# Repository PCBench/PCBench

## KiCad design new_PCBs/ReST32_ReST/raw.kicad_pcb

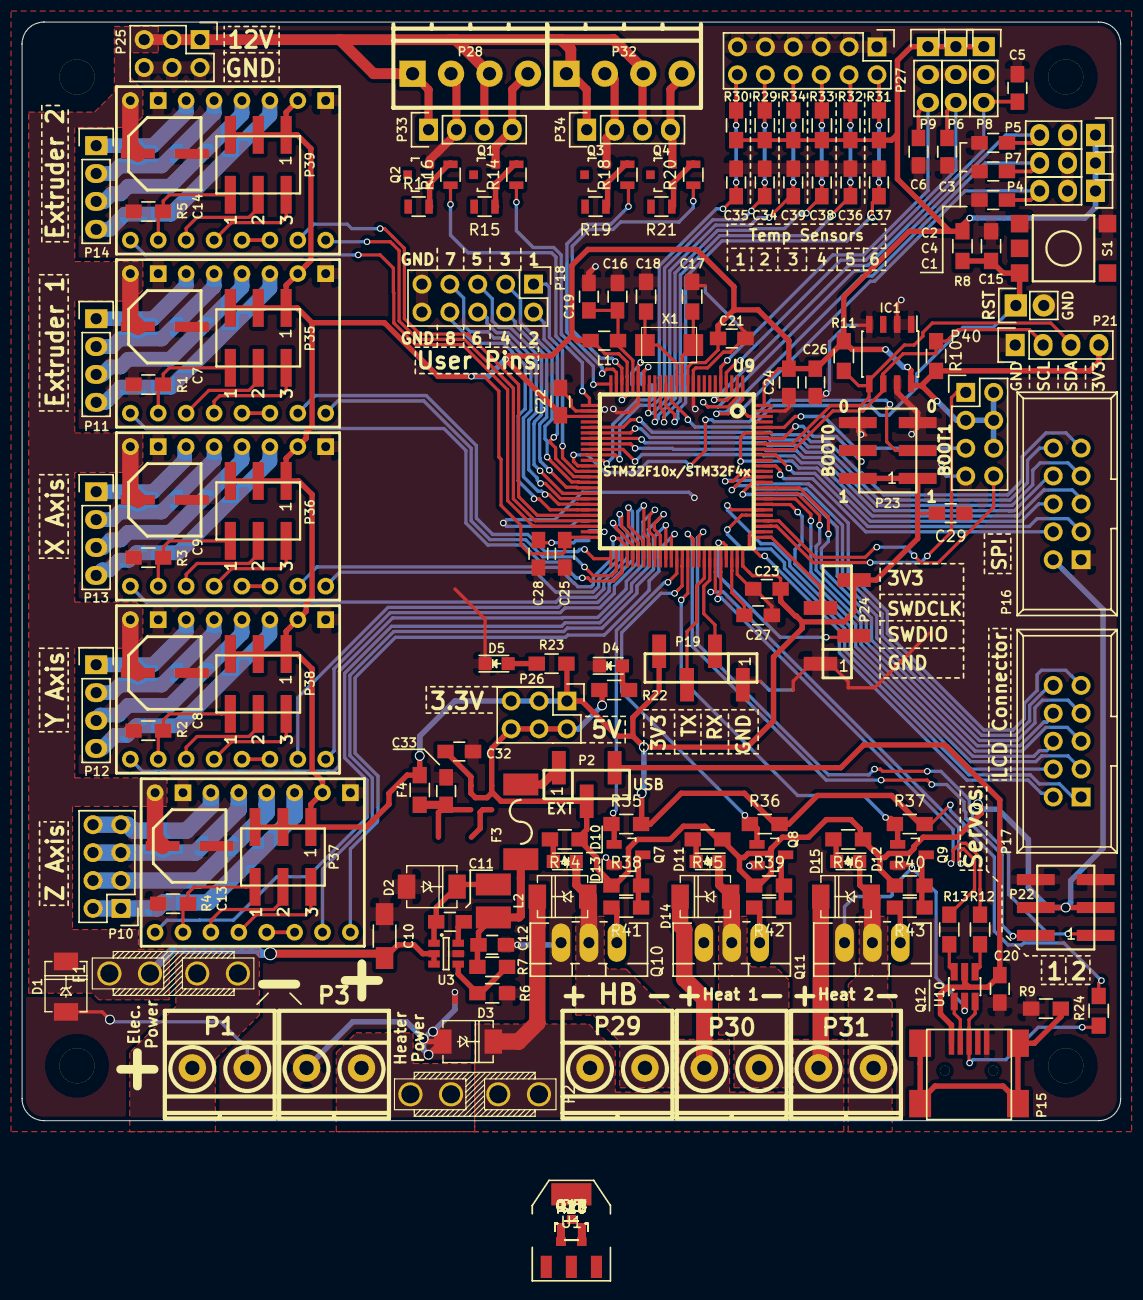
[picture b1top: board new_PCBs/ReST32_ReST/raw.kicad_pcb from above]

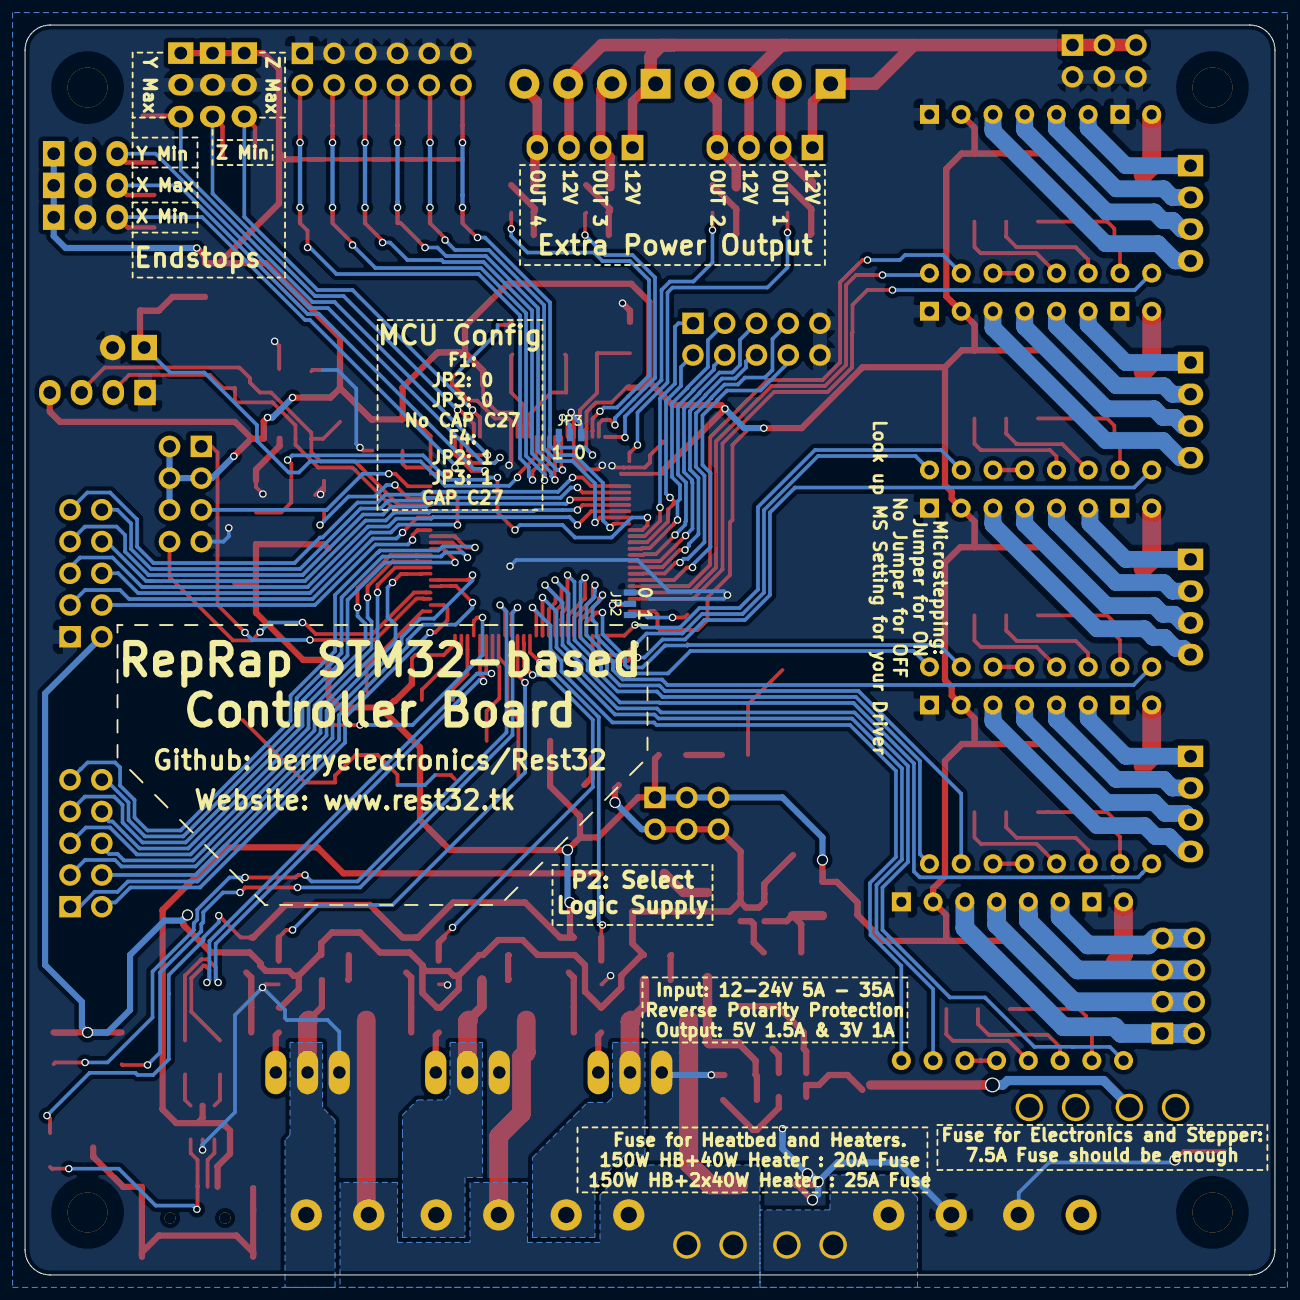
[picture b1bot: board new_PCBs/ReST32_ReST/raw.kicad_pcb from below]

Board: 2 copper layers, 100.0 x 100.0 mm, 168 parts (2 on the bottom side), 168 nets.

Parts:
C1, C2, C3, C4, C5, C6: 10nF; C_0805_HandSoldering
C7, C8, C9, C13, C14: 100uF; CP-PANASONIC-SMT_D8
C10: 10uF; C_1206_HandSoldering
C11: 22nF; C_0805_HandSoldering
C12, C26: 4.7uF; C_0805_HandSoldering
C15: 100nF; R_0805_HandSoldering
C16, C32, C33, C34, C35, C36, C37, C38, C39: 10uF; C_0805_HandSoldering
C17, C18: 10pF; R_0805_HandSoldering
C19, C20, C21, C22, C23, C24, C25, C29: 100nF; C_0805_HandSoldering
C27, C28: 2u2; C_0805_HandSoldering
D1, D3: 1N400x; DO-214AC.SMA
D2: B240A; DO-214AC.SMA
D4, D5, D10, D11, D12: LED; LED_0805
D13, D14, D15: D_1N400x-SMD; DO-214AC.SMA
F1, F2: F_Small; MINI-FUSE
F3: F_Small; FUSE-1812
F4: F_Small; R_0805_HandSoldering
IC1: AT24C256; SOIC-8_3.9x4.9mm_Pitch1.27mm
JP2, JP3: JUMPER3; S_JUMPER_3
L1: BEAD; C_0805_HandSoldering
L2: 4.7uH; CD32
P1, P3, P29, P30, P31: CONN_01X02; screw-5-2P
P2: CONN_01X03; bb02-hy03a
P4, P5, P6, P7, P8, P9: CONN_01X03; Pin_Header_Straight_1x03
P10, P40: CONN_02X04; Pin_Header_Straight_2x04
P11, P12, P13, P14, P21: CONN_01X04; Pin_Header_Straight_1x04
P15: USB_OTG; USB_Mini-B
P16, P17: CONN_02X05; IDC_Header_Straight_10pins
P18: CONN_02X05; Pin_Header_Straight_2x05
P19, P24: CONN_01X04; bb02-hy04a
P20: CONN_01X02; Pin_Header_Straight_1x02
P22, P23, P35, P36, P37, P38, P39: CONN_02X03; bb02-hp06
P25, P26: CONN_02X03; Pin_Header_Straight_2x03
P27: CONN_02X06; Pin_Header_Straight_2x06
P28, P32: CONN_02X02; pt_1,5-4-3,5-h
P33, P34: CONN_02X02; Pin_Header_Straight_1x04
Q1, Q2, Q3, Q4, Q7, Q8, Q9: BSS138; SOT-23
Q5, Q6, Q13, Q14: BSS316; SOT-23
Q10, Q11, Q12: Q_AOT240L; TO-220_Neutral123_Vertical_LargePads
R1, R2, R3, R4, R5, R35, R36, R37, R38, R39, R40: 100K; R_0805_HandSoldering
R6: 28.7k; R_0805_HandSoldering
R7: 150K; R_0805_HandSoldering
R8: 10K; R_0805_HandSoldering
R9: 1M; R_0805_HandSoldering
R10, R11, R29, R30, R31, R32, R33, R34: 4K7; R_0805_HandSoldering
R12, R13, R41, R42, R43: 22R; R_0805_HandSoldering
R14, R16, R18, R20: 22R; R_0805
R15, R17, R19, R21, R25, R26, R27, R28: 100K; R_0805
R22, R23, R44, R45, R46: 1K; R_0805_HandSoldering
R24: 1K5; R_0805_HandSoldering
S1: SW_DIP_x2; SMD-BUTTON-6MM
U1: AMS1117; SOT-223
U2, U5, U6, U7, U8: POLOLU_A4988; SWDIP8_.6W
U3: ACT4088; SOT-23-6
U9: STM32F10x/STM32F4x; LQFP100-14x14
U10: USBLC6-2; SOT32-6L
X1: Crystal_Small; 2P-5032

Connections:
+3V3: C21.1, C22.1, C23.1, C24.1, C25.1, C26.1, C29.2, F4.1, IC1.8, JP3.1, L1.1, P4.1, P5.1, P6.1, P7.1, P8.1, P9.1, P19.4, P21.4, P23.1, P23.2, P24.4, P26.1, P26.3, P26.5, P35.1, P35.3, P35.5, P36.1, P36.3, P36.5, P37.1, P37.3, P37.5, P38.1, P38.3, P38.5, P39.1, P39.3, P39.5, P40.2, P40.3, P40.4, P40.6, R8.2, R10.2, R11.2, R15.1, R17.2, R19.1, R21.1, R23.1, R24.2, R29.2, R30.2, R31.2, R32.2, R33.2, R34.2, R35.2, R36.2, R37.2, U2.2, U5.2, U6.2, U7.2, U8.2, U9.11, U9.22, U9.28, U9.50, U9.75, U9.100
+5V: C32.2, P2.2, P16.2, P22.3, P22.4, P26.2, P26.4, P26.6, R22.1, R25.2, R26.1, R27.1, R28.1, R38.1, R39.1, R40.1, R44.1, R45.1, R46.1, U1.3
+12V: C7.1, C8.1, C9.1, C10.1, C13.1, C14.1, D1.1, F1.2, P25.1, P25.3, P25.5, P28.1, P28.3, P32.1, P32.3, P33.1, P33.3, P34.1, P34.3, U2.8, U3.2, U3.3, U5.8, U6.8, U7.8, U8.8
+12VA: D3.1, D13.1, D14.1, D15.1, F2.2, P29.1, P30.1, P31.1
/Extra Power Output/EXTRA_0_5V: Q1.3, Q5.1, R25.1
/Extra Power Output/EXTRA_0_OUT: P28.2, P33.2, Q5.3
/Extra Power Output/EXTRA_1_5V: Q3.3, Q13.1, R27.2
/Extra Power Output/EXTRA_1_OUT: P28.4, P33.4, Q13.3
/Extra Power Output/EXTRA_2_5V: Q2.3, Q6.1, R26.2
/Extra Power Output/EXTRA_2_OUT: P32.2, P34.2, Q6.3
/Extra Power Output/EXTRA_3_5V: Q4.3, Q14.1, R28.2
/Extra Power Output/EXTRA_3_OUT: P32.4, P34.4, Q14.3
/Heater/H0_GATE: Q7.1, R41.2
/Heater/H1_GATE: Q8.1, R42.2
/Heater/H2_GATE: Q9.1, R43.2
/Heater/HEATER_0_5VL: Q7.3, Q10.1, R38.2
/Heater/HEATER_0_OUT: D10.1, D13.2, P29.2, Q10.2
/Heater/HEATER_1_5VL: Q8.3, Q11.1, R39.2
/Heater/HEATER_1_OUT: D11.1, D14.2, P30.2, Q11.2
/Heater/HEATER_2_5VL: Q9.3, Q12.1, R40.2
/Heater/HEATER_2_OUT: D12.1, D15.2, P31.2, Q12.2
/Logic/USBP_D+: P15.3, R24.1, U10.3
/Logic/USBP_D-: P15.2, U10.1
/Logic/USBR+: R12.1, U10.4
/Logic/USBR-: R13.2, U10.6
/Power Input/12V-R: F1.1, P1.1
/Power Input/12VA-R: F2.1, P3.2
/Stepper and Endstop/E0M1: P35.6, R1.1, U2.10
/Stepper and Endstop/E0M2: P35.4, U2.11
/Stepper and Endstop/E0M3: P35.2, U2.12
/Stepper and Endstop/E0_1A: P11.3, U2.4
/Stepper and Endstop/E0_1B: P11.4, U2.3
/Stepper and Endstop/E0_2A: P11.2, U2.5
/Stepper and Endstop/E0_2B: P11.1, U2.6
/Stepper and Endstop/E1M1: P39.6, R5.1, U8.10
/Stepper and Endstop/E1M2: P39.4, U8.11
/Stepper and Endstop/E1M3: P39.2, U8.12
/Stepper and Endstop/E1_1A: P14.3, U8.4
/Stepper and Endstop/E1_1B: P14.4, U8.3
/Stepper and Endstop/E1_2A: P14.2, U8.5
/Stepper and Endstop/E1_2B: P14.1, U8.6
/Stepper and Endstop/XM1: P36.6, R3.1, U6.10
/Stepper and Endstop/XM2: P36.4, U6.11
/Stepper and Endstop/XM3: P36.2, U6.12
/Stepper and Endstop/X_1A: P13.3, U6.4
/Stepper and Endstop/X_1B: P13.4, U6.3
/Stepper and Endstop/X_2A: P13.2, U6.5
/Stepper and Endstop/X_2B: P13.1, U6.6
/Stepper and Endstop/YM1: P38.6, R2.1, U5.10
/Stepper and Endstop/YM2: P38.4, U5.11
/Stepper and Endstop/YM3: P38.2, U5.12
/Stepper and Endstop/Y_1A: P12.3, U5.4
/Stepper and Endstop/Y_1B: P12.4, U5.3
/Stepper and Endstop/Y_2A: P12.2, U5.5
/Stepper and Endstop/Y_2B: P12.1, U5.6
/Stepper and Endstop/ZM1: P37.6, R4.1, U7.10
/Stepper and Endstop/ZM2: P37.4, U7.11
/Stepper and Endstop/ZM3: P37.2, U7.12
/Stepper and Endstop/Z_1A: P10.3, P10.4, U7.4
/Stepper and Endstop/Z_1B: P10.1, P10.2, U7.3
/Stepper and Endstop/Z_2A: P10.5, P10.6, U7.5
/Stepper and Endstop/Z_2B: P10.7, P10.8, U7.6
BOOT_0: P23.4, U9.94
BOOT_1: P23.3, U9.37
DISPLAY_CD: P17.2, U9.77
DISPLAY_CS: P17.1, U9.80
DISPLAY_D0: P17.4, U9.81
DISPLAY_D1: P17.3, U9.82
DISPLAY_D2: P17.6, U9.83
DISPLAY_D3: P17.5, U9.84
DISPLAY_D4: P17.8, U9.85
DISPLAY_D5: P17.7, U9.86
DISPLAY_D6: P17.10, U9.87
DISPLAY_D7: P17.9, U9.88
DISPLAY_EXTRA_0: P16.6, U9.95
DISPLAY_EXTRA_1: P40.5, U9.96
DISPLAY_RD: P16.3, U9.91
DISPLAY_WR: P16.4, U9.89
ENDSTOP_X_MAX: C4.1, P7.3, U9.1
ENDSTOP_X_MIN: C1.1, P4.3, U9.98
ENDSTOP_Y_MAX: C5.1, P8.3, U9.3
ENDSTOP_Y_MIN: C2.1, P5.3, U9.2
ENDSTOP_Z_MAX: C6.1, P9.3, U9.5
ENDSTOP_Z_MIN: C3.1, P6.3, U9.4
EXTRA_0: R16.1, U9.26
EXTRA_1: R14.1, U9.25
EXTRA_2: R18.1, U9.24
EXTRA_3: R20.1, U9.23
GND: C1.2, C2.2, C3.2, C4.2, C5.2, C6.2, C7.2, C8.2, C9.2, C10.2, C12.2, C13.2, C14.2, C15.1, C16.2, C17.1, C18.2, C19.2, C20.2, C21.2, C22.2, C23.2, C24.2, C25.2, C26.2, C27.2, C28.2, C29.1, C32.1, C33.2, C34.2, C35.2, C36.2, C37.2, C38.2, C39.2, D1.2, D2.2, D3.2, D4.1, D5.1, IC1.1, IC1.2, IC1.4, IC1.7, JP2.3, JP3.3, P1.2, P3.1, P4.2, P5.2, P6.2, P7.2, P8.2, P9.2, P15.5, P16.1, P18.9, P18.10, P19.1, P20.2, P21.1, P22.5, P22.6, P23.5, P23.6, P24.1, P25.2, P25.4, P25.6, P27.1, P27.3, P27.5, P27.7, P27.9, P27.11, P40.7, Q1.2, Q2.2, Q3.2, Q4.2, Q5.2, Q6.2, Q7.2, Q8.2, Q9.2, Q10.3, Q11.3, Q12.3, Q13.2, Q14.2, R1.2, R2.2, R3.2, R4.2, R5.2, R6.1, R9.1, S1.3, S1.4, U1.1, U2.1, U2.7, U3.5, U5.1, U5.7, U6.1, U6.7, U7.1, U7.7, U8.1, U8.7, U9.10, U9.20, U9.27, U9.74, U9.99, U10.2
HEATER_0: R35.1, R41.1, U9.63
HEATER_1: R36.1, R42.1, U9.64
HEATER_2: R37.1, R43.1, U9.65
I2C_SCL: IC1.6, P21.2, R10.1, U9.92
I2C_SDA: IC1.5, P21.3, R11.1, U9.93
unnamed: C11.1, D2.1, L2.1, U3.1
unnamed: C11.2, U3.6
unnamed: C12.1, F3.2, L2.2, R7.2
unnamed: C16.1, C19.1, L1.2, U9.21
unnamed: C17.2, U9.12, X1.2
unnamed: C18.1, U9.13, X1.1
unnamed: C28.1, JP2.1
unnamed: C33.1, F4.2, U1.2
unnamed: D4.2, R22.2
unnamed: D5.2, R23.2
unnamed: D10.2, R44.2
unnamed: D11.2, R45.2
unnamed: D12.2, R46.2
unnamed: P15.6, R9.2
unnamed: Q1.1, R16.2, R17.1
unnamed: Q2.1, R18.2, R19.2
unnamed: Q3.1, R14.2, R15.2
unnamed: Q4.1, R20.2, R21.2
unnamed: R6.2, R7.1, U3.4
unnamed: U2.13, U2.14
unnamed: U5.13, U5.14
unnamed: U6.13, U6.14
unnamed: U7.13, U7.14
unnamed: U8.13, U8.14
P_VCAP_1: JP2.2, U9.49
P_VCAP_2: C27.1, U9.73
P_VSSA: JP3.2, U9.19
RESET: C15.2, P20.1, R8.1, S1.2, U9.14
SERVO_0: P22.2, U9.66
SERVO_1: P22.1, U9.67
SPI_CS1: P16.8, U9.33
SPI_CS2: P16.5, U9.34
SPI_MISO: P16.10, U9.31
SPI_MOSI: P16.7, U9.32
SPI_SCK: P16.9, U9.30
STEPPER_E_0_DIR: U2.16, U9.52
STEPPER_E_0_EN: U2.9, U9.53
STEPPER_E_0_STEP: U2.15, U9.51
STEPPER_E_1_DIR: U8.16, U9.47
STEPPER_E_1_EN: U8.9, U9.48
STEPPER_E_1_STEP: U8.15, U9.46
STEPPER_X_DIR: U6.16, U9.55
STEPPER_X_EN: U6.9, U9.56
STEPPER_X_STEP: U6.15, U9.54
STEPPER_Y_DIR: U5.16, U9.58
STEPPER_Y_EN: U5.9, U9.59
STEPPER_Y_STEP: U5.15, U9.57
STEPPER_Z_DIR: U7.16, U9.62
STEPPER_Z_EN: U7.9, U9.60
STEPPER_Z_STEP: U7.15, U9.61
SWD_CLK: P24.3, U9.76
SWD_IO: P24.2, U9.72
TEMP_0: C37.1, P27.2, R31.1, U9.15
TEMP_1: C36.1, P27.4, R32.1, U9.16
TEMP_2: C38.1, P27.6, R33.1, U9.17
TEMP_3: C39.1, P27.8, R34.1, U9.18
TEMP_4: C34.1, P27.10, R29.1, U9.35
TEMP_5: C35.1, P27.12, R30.1, U9.36
UART_1_RX: P19.2, U9.69
UART_1_TX: P19.3, U9.68
UART_4_RX: P40.8, U9.79
UART_4_TX: P40.1, U9.78
USB_MCU+: R12.2, U9.71
USB_MCU-: R13.1, U9.70
USER_0: P18.1, U9.38
USER_1: P18.2, U9.39
USER_2: P18.3, U9.40
USER_3: P18.4, U9.41
USER_4: P18.5, U9.42
USER_5: P18.6, U9.43
USER_6: P18.7, U9.44
USER_7: P18.8, U9.45
VCC: C20.1, P2.3, P15.1, U10.5
VEE: F3.1, P2.1

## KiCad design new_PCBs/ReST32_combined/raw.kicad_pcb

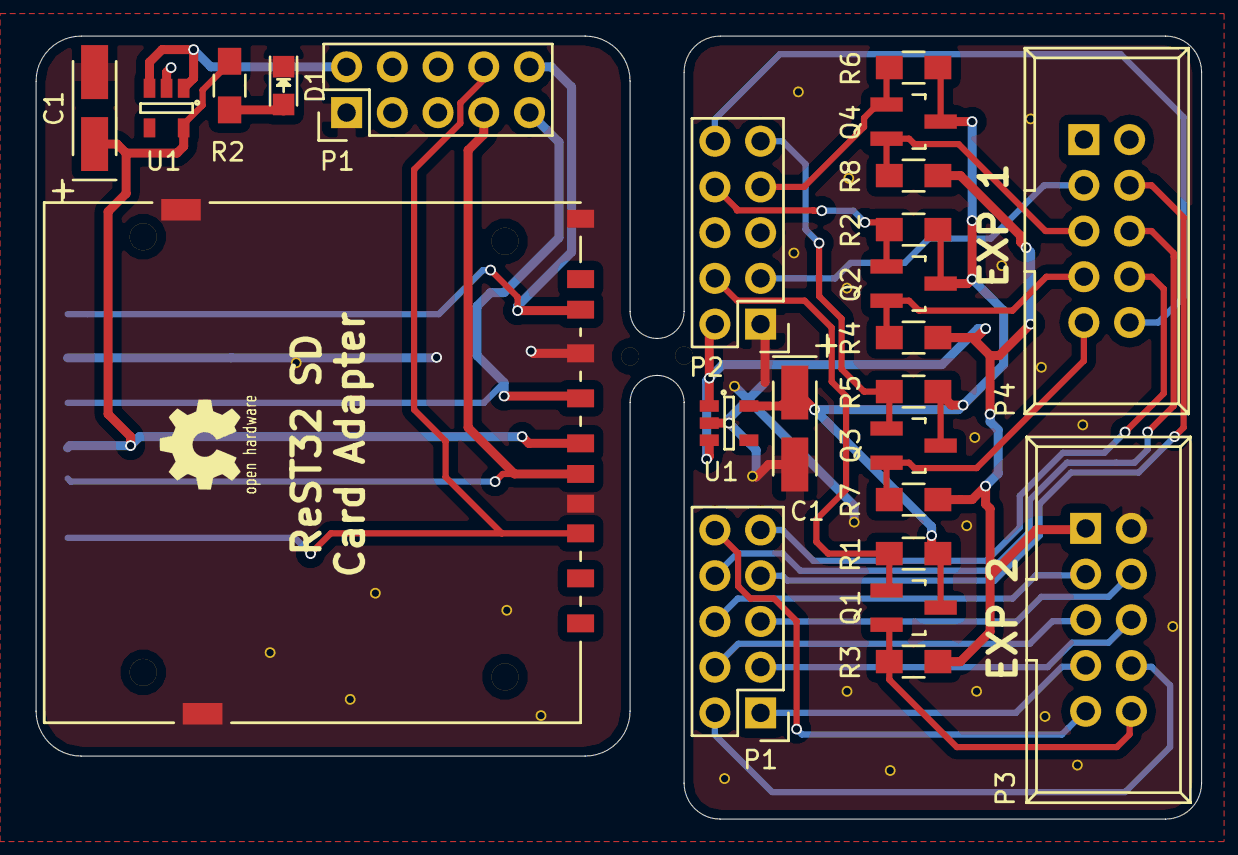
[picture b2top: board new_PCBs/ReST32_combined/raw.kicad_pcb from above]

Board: 2 copper layers, 64.8 x 43.5 mm, 25 parts (1 on the bottom side), 28 nets.

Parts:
C1: 2.2uF; TantalC_SizeA_EIA-3216_HandSoldering
C1#2: CP1_Small; TantalC_SizeA_EIA-3216_HandSoldering
CON1, CON2: uSD_Card; SD_Card_Receptacle
D1: Led_Small; LED_0805
P1, P1#2, P2: CONN_02X05; Pin_Header_Straight_2x05
P3, P4: CONN_02X05; IDC_Header_Straight_10pins
Q1, Q2, Q3, Q4: BSS138; SOT-23_Handsoldering
R1, R2, R3, R4, R5, R6, R7, R8: 10K; R_0805_HandSoldering
R2#2: 1K; R_0805_HandSoldering
U1, U1#2: MIC5205; SOT-23-5

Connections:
+3V3: C1.1, C1#2.1, CON1.4, CON2.4, Q1.3, Q2.3, Q3.3, Q4.3, R1.1, R2.1, R2#2.1, R5.1, R6.1, U1.5, U1#2.5
+5V: P1#2.2, P2.2, P3.1, R3.1, R4.1, R7.1, R8.1, U1.1, U1.3, U1#2.1, U1#2.3
/BEEP: P3.10, Q1.2, R3.2
/CS: P4.7, Q2.2, R4.2
/DISPLAY_CD: P1.2, P3.8
/DISPLAY_CS: P1.1, P3.7
/DISPLAY_D0: P1.4, P3.5
/DISPLAY_D1: P1.3, P3.6
/DISPLAY_D2: P1.6, P3.3
/DISPLAY_D3: P1.5, P3.4
/DISPLAY_D4: P1.8, P4.6
/DISPLAY_D5: P1.7, P4.4
/DISPLAY_D6: P1.10, P3.9
/DISPLAY_D7: P1.9, P4.8
/DISPLAY_RD: P2.3, P4.3
/DISPLAY_WR: P2.4, Q1.1, R1.2
/MISO: P2.10, P4.10
/MOSI: P4.5, Q4.2, R8.2
/SCK: P4.9, Q3.2, R7.2
/SPI-CS: CON1.2, CON2.2, P1#2.8
/SPI-MISO: CON1.7, CON2.7, P1#2.10
/SPI-MOSI: CON1.3, CON2.3, P1#2.7
/SPI-SCK: CON1.5, CON2.5, P1#2.9
/SPI_CS1: P2.8, Q2.1, R2.2
/SPI_MOSI: P2.7, Q4.1, R6.2
/SPI_SCK: P2.9, Q3.1, R5.2
GND: C1.2, C1#2.2, CON1.6, CON1.10, CON1.11, CON1.12, CON1.13, CON2.6, CON2.10, CON2.11, CON2.12, CON2.13, D1.1, P1#2.1, P2.1, P3.2, U1.2, U1#2.2
unnamed: D1.2, R2#2.2

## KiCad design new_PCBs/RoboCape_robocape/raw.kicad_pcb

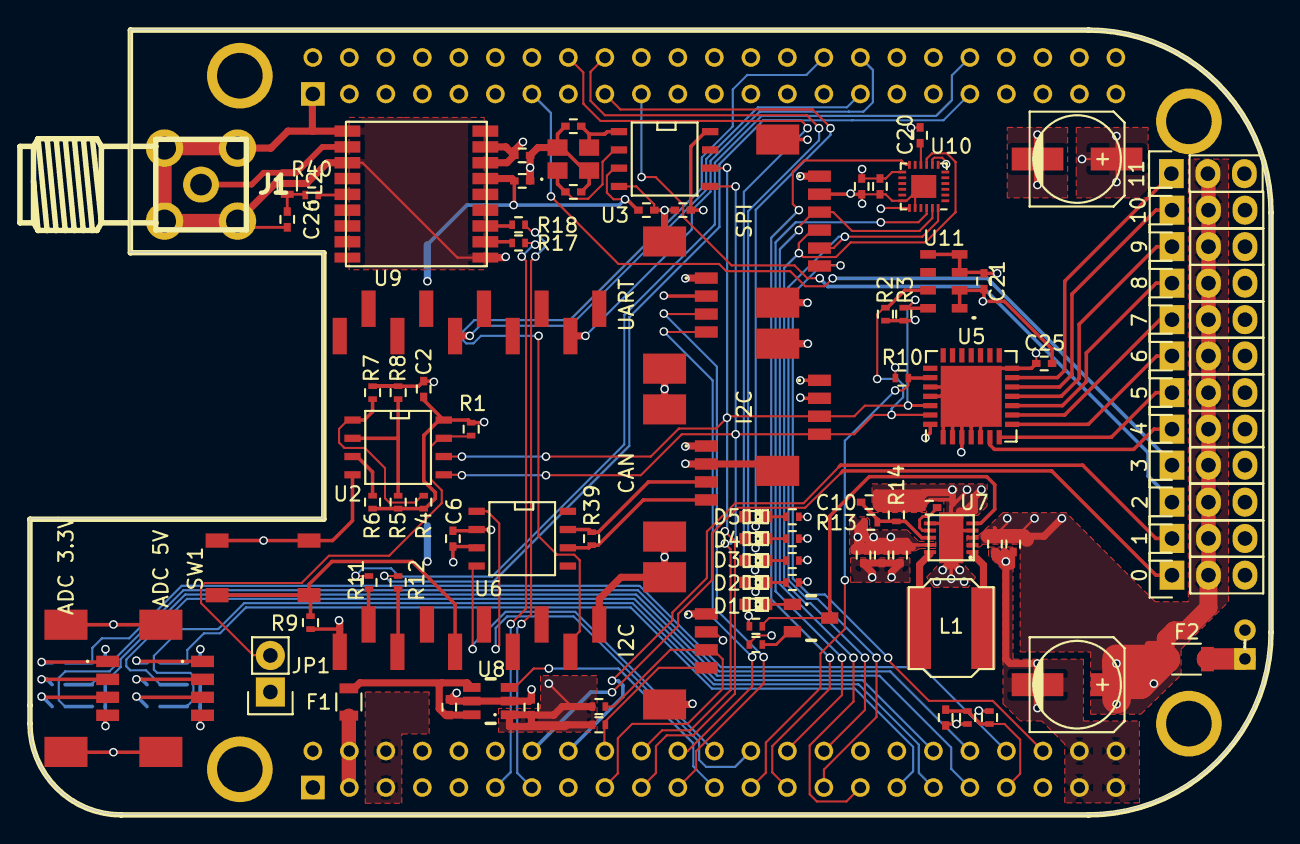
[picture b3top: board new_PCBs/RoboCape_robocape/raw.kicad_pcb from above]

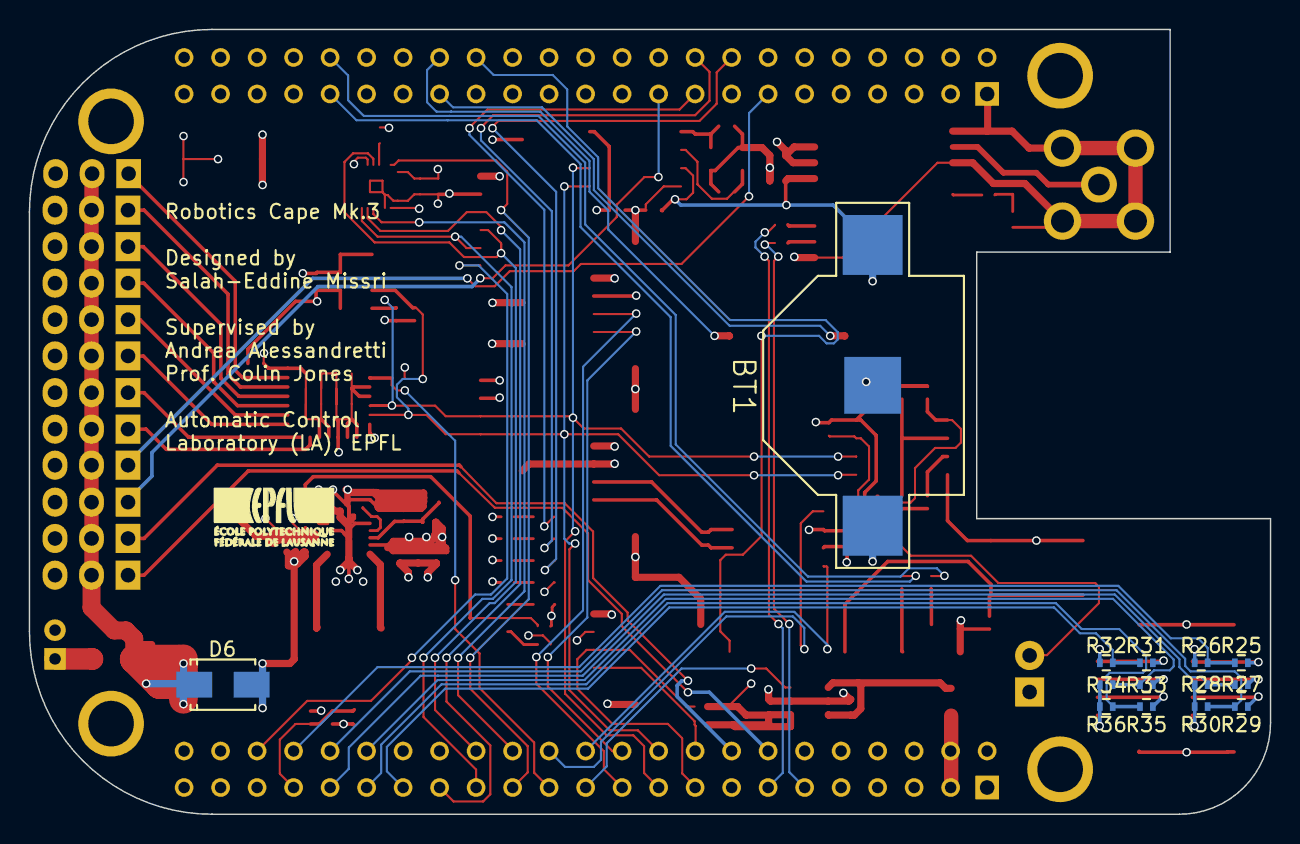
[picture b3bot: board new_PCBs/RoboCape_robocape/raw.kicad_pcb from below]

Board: 4 copper layers, 86.4 x 54.6 mm, 113 parts (14 on the bottom side), 87 nets.

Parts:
0, 1, 2, 3, 4, 5, 6, 7, 8, 9, 10, 11: SERVO; Pin_Header_Straight_1x03
BT1: 1.4V to 3.6V; BK-885
C1, C14, C15: 1u; C_0402
C2, C6, C9, C17, C20, C21, C22, C25: 100n; C_0402
C3: 220n; C_0402
C4, C5, C10: 10p; C_0402
C7, C8: 10u; C_0402
C11, C12, C13: 22u; C_0402
C16, C19: 0.1u; C_0402
C18: 10n; C_0402
C23, C24: 100u; c_elec_6.3x7.7
C26: C; C_0402
CONN1: UART; _Molex-PicoBlade-SMD-4
CONN5, CONN17: I2C; _Molex-PicoBlade-SMD-4
CONN9: CAN; _Molex-PicoBlade-SMD-4
CONN16: PWR; _Pin2mm_2
CONN18: SPI; _Molex-PicoBlade-SMD-6
CONN19: ADC 3.3V; _Molex-PicoBlade-SMD-4
CONN20: ADC 5V; _Molex-PicoBlade-SMD-4
D1: YELLOW; LED-0603
D2: WHITE; LED-0603
D3: GREEN; LED-0603
D4: BLUE; LED-0603
D5: RED; LED-0603
D6: ZENER 12V; Diode-SMA_Standard
F1: 500mA; R_0805
F2: 10A; R_1206
J1: SMA; SMA-CONN
JP1: Jumper_NC_Small; Pin_Header_Straight_1x02
L1: 1uH; Laird_TYS6045
L2: L; R_0603
Q1: 2N7002; _SOT23-3
R1, R10: 10k; R_0402
R2, R3, R4, R5, R6, R23, R24, R37: 4.7k; R_0402
R7, R8: 0; R_0402
R9: 50k; R_0402
R11, R12, R17, R18: 330; R_0402
R13, R15: 1M; R_0402
R14: 111k; R_0402
R16, R19, R20, R21, R22: 1k; R_0402
R25, R27, R29: 680; R_0402
R26, R28, R30, R32, R34, R36, R38: 820; R_0402
R31, R33, R35: 1.47k; R_0402
R39: 120; R_0402
R40: 10; R_0402
SW1: SW_PUSH; _PTS525SK15-SMT-Pushbutton
U1: BEAGLEBONE
U2: CAT24C256W; SOIC-8-N
U3: BQ32000; SOIC-8-N
U4: XBee_Header; Xbee_Header_SMD
U5: PCA9685; QFN-28-1EP_6x6mm_Pitch0.65mm
U6: SN65HVD232D; SOIC-8-N
U7: TPS63060; SON-10
U8: TPS22929D; _TSOT23-6
U9: MAX-M8
U10: MPU-9250; QFN-24-1EP_3x3mm_Pitch0.4mm
U11: MS5611-01BA; _MS5611-01BA
X1: 32768Hz; _TSX-3225-SMD-XTAL

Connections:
+3.3V_A: C1.1, C2.1, C15.1, C17.1, C18.1, C21.1, C25.1, CONN5.1, CONN17.1, D2.2, R1.1, R2.1, R3.1, R4.1, R5.1, R6.1, R10.1, R23.1, R24.1, U2.8, U3.8, U5.28, U8.1, U10.8, U10.13, U10.19, U11.1, U11.2
+3V3: C6.1, C16.1, F1.1, R9.1, U1.C3, U1.C4, U4.1, U6.3, U9.7, U9.8
+5V: C11.1, C12.1, C13.1, CONN1.1, CONN9.1, CONN18.1, D1.2, R13.1, R15.1, U1.C5, U1.C6, U7.9
/Connectivity/ADC_1: R25.2, R26.1, U1.C40
/Connectivity/ADC_2: R27.2, R28.1, U1.C37
/Connectivity/ADC_3: R29.2, R30.1, U1.C38
/Connectivity/ADC_4: R31.2, R32.1, U1.C33
/Connectivity/ADC_5: R33.2, R34.1, U1.C36
/Connectivity/ADC_6: R35.2, R36.1, U1.C35
/Connectivity/CAN_RX: U1.C24, U6.4
/Connectivity/CAN_TX: U1.C26, U6.1
/Connectivity/I2C1_SCL: CONN17.3, R24.2, U1.C17
/Connectivity/I2C1_SDA: CONN17.4, R23.2, U1.C18
/Connectivity/I2C2_SCL: CONN5.3, R3.2, U1.C19, U2.6, U3.6, U5.26, U11.8
/Connectivity/I2C2_SDA: CONN5.4, R2.2, U1.C20, U2.5, U3.5, U5.27, U11.7
/Connectivity/PWMGEN_OE: R10.2, U1.C25, U5.23
/Connectivity/PWM_0: 0.1, U1.C14
/Connectivity/PWM_1: 1.1, U1.C16
/Connectivity/PWM_2: 2.1, U1.B19
/Connectivity/PWM_3: 3.1, U1.B13
/Connectivity/PWM_4: 4.1, U5.6
/Connectivity/PWM_5: 5.1, U5.7
/Connectivity/PWM_6: 6.1, U5.8
/Connectivity/PWM_7: 7.1, U5.9
/Connectivity/PWM_8: 8.1, U5.10
/Connectivity/PWM_9: 9.1, U5.11
/Connectivity/PWM_10: 10.1, U5.12
/Connectivity/PWM_11: 11.1, U5.13
/Connectivity/SPI1_CS1: CONN18.6, U1.C42
/Connectivity/UART_EXT_RX: CONN1.4, U1.C22
/Connectivity/UART_EXT_TX: CONN1.3, U1.C21
/Connectivity/XBEE_CTS: U1.B32, U4.12
/Connectivity/XBEE_DTR: U1.B30, U4.9
/Connectivity/XBEE_RTS: U1.B31, U4.16
/Connectivity/XBEE_RX: R12.1, U1.B37
/Connectivity/XBEE_TX: R11.1, U1.B38
/ERROR_LED: D5.2, U1.B17
/HEARTBEAT_LED: D3.2, U1.B16
/Power/3.3V_A_EN: U1.C23, U8.3
/Power/Back_Bat: BT1.1, C3.1, C19.1, U3.3, U9.6
/Power/PWR_GOOD: Q1.2, R15.2, U7.5
/Power/PWR_VOLTAGE_SENSE: C22.1, R37.2, R38.1, U1.C39
/STATUS_LED: D4.2, U1.B18
/Sensors/GPS_RX: R18.1, U1.C13
/Sensors/GPS_TX: R17.1, U1.C11
/Sensors/MPU9250_CS: U1.C28, U10.22
/Sensors/MPU9250_INT: U1.C27, U10.12
/Sensors/MPU9250_MISO: CONN18.4, U1.C30, U10.9
/Sensors/MPU9250_MOSI: CONN18.5, U1.C29, U10.24
/Sensors/MPU9250_SCK: CONN18.3, U1.C31, U10.23
GND: 0.3, 1.3, 2.3, 3.3, 4.3, 5.3, 6.3, 7.3, 8.3, 9.3, 10.3, 11.3, BT1.2, C1.2, C2.2, C3.2, C4.2, C5.2, C6.2, C7.2, C8.2, C9.2, C10.2, C11.2, C12.2, C13.2, C14.2, C15.2, C16.2, C17.2, C18.2, C19.2, C20.2, C21.2, C22.2, C23.2, C24.2, C25.2, C26.2, CONN1.2, CONN1.MECH, CONN5.2, CONN5.MECH, CONN9.2, CONN9.MECH, CONN16.2, CONN17.2, CONN17.MECH, CONN18.2, CONN18.MECH, CONN19.4, CONN19.MECH, CONN20.4, CONN20.MECH, D6.2, J1.2, J1.3, J1.4, J1.5, JP1.1, R7.2, R8.2, R14.2, R16.2, R19.1, R20.1, R21.1, R22.1, R26.2, R28.2, R30.2, R32.2, R34.2, R36.2, R38.2, SW1.1, U1.B1, U1.B2, U1.C1, U1.C2, U1.C34, U1.C43, U1.C44, U1.C45, U1.C46, U2.4, U3.4, U4.10, U5.1, U5.2, U5.3, U5.4, U5.5, U5.14, U5.24, U5.25, U5.29, U6.2, U7.4, U7.7, U7.11, U8.2, U8.5, U9.1, U9.10, U9.12, U10.18, U10.20, U10.25, U11.3, U11.4, U11.5, X1.2, X1.4
unnamed: C4.1, U3.2, X1.1
unnamed: C5.1, U3.1, X1.3
unnamed: C9.1, U7.6
unnamed: C10.1, R13.2, R14.1, U7.8
unnamed: C14.1, F1.2, U8.4, U8.6
unnamed: C20.1, U10.10
unnamed: C26.1, L2.2, R40.1
unnamed: CONN9.3, R39.1, U6.7
unnamed: CONN9.4, R39.2, U6.6
unnamed: CONN16.1, F2.1
unnamed: CONN19.1, R25.1
unnamed: CONN19.2, R27.1
unnamed: CONN19.3, R29.1
unnamed: CONN20.1, R31.1
unnamed: CONN20.2, R33.1
unnamed: CONN20.3, R35.1
unnamed: D1.1, Q1.1
unnamed: D2.1, R19.2
unnamed: D3.1, R20.2
unnamed: D4.1, R21.2
unnamed: D5.1, R22.2
unnamed: J1.1, L2.1, U9.11
unnamed: JP1.2, R1.2, U2.7
unnamed: L1.1, U7.1
unnamed: L1.2, U7.10
unnamed: Q1.3, R16.1
unnamed: R4.2, R7.1, U2.1
unnamed: R5.2, R8.1, U2.2
unnamed: R6.2, U2.3
unnamed: R9.2, SW1.2, U4.5
unnamed: R11.2, U4.2
unnamed: R12.2, U4.3
unnamed: R17.2, U9.2
unnamed: R18.2, U9.3
unnamed: R40.2, U9.14
POWER: 0.2, 1.2, 2.2, 3.2, 4.2, 5.2, 6.2, 7.2, 8.2, 9.2, 10.2, 11.2, C7.1, C8.1, C23.1, C24.1, D6.1, F2.2, R37.1, U7.2, U7.3

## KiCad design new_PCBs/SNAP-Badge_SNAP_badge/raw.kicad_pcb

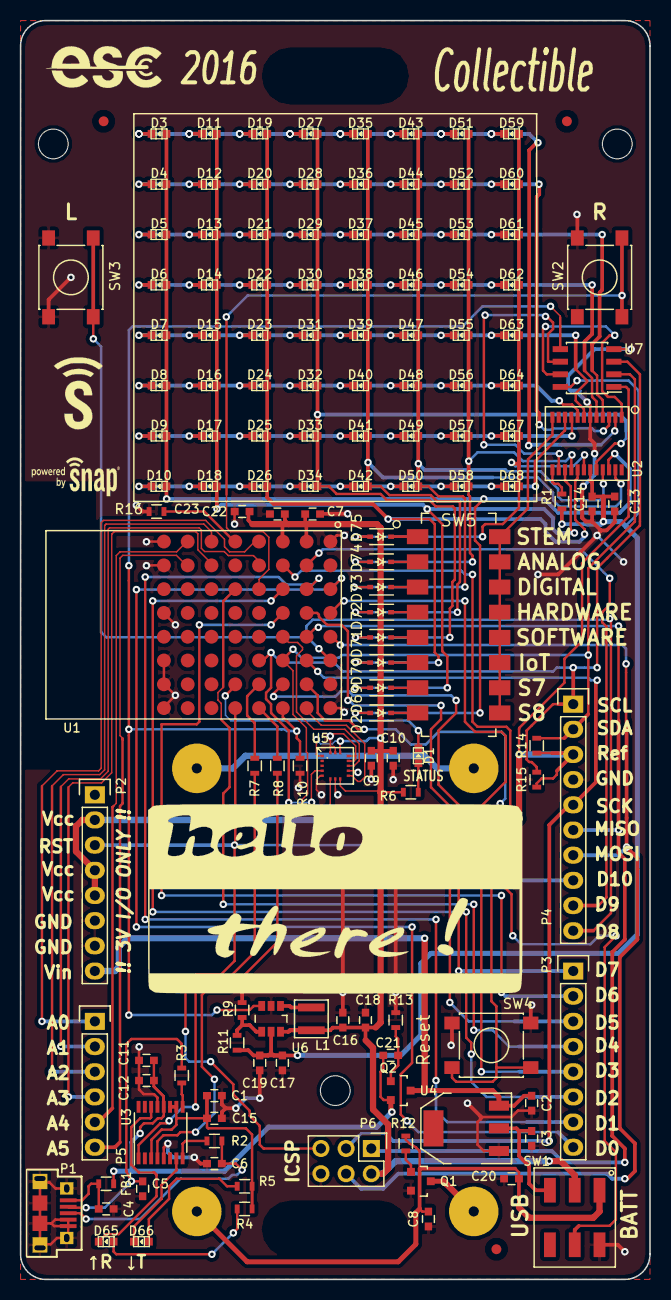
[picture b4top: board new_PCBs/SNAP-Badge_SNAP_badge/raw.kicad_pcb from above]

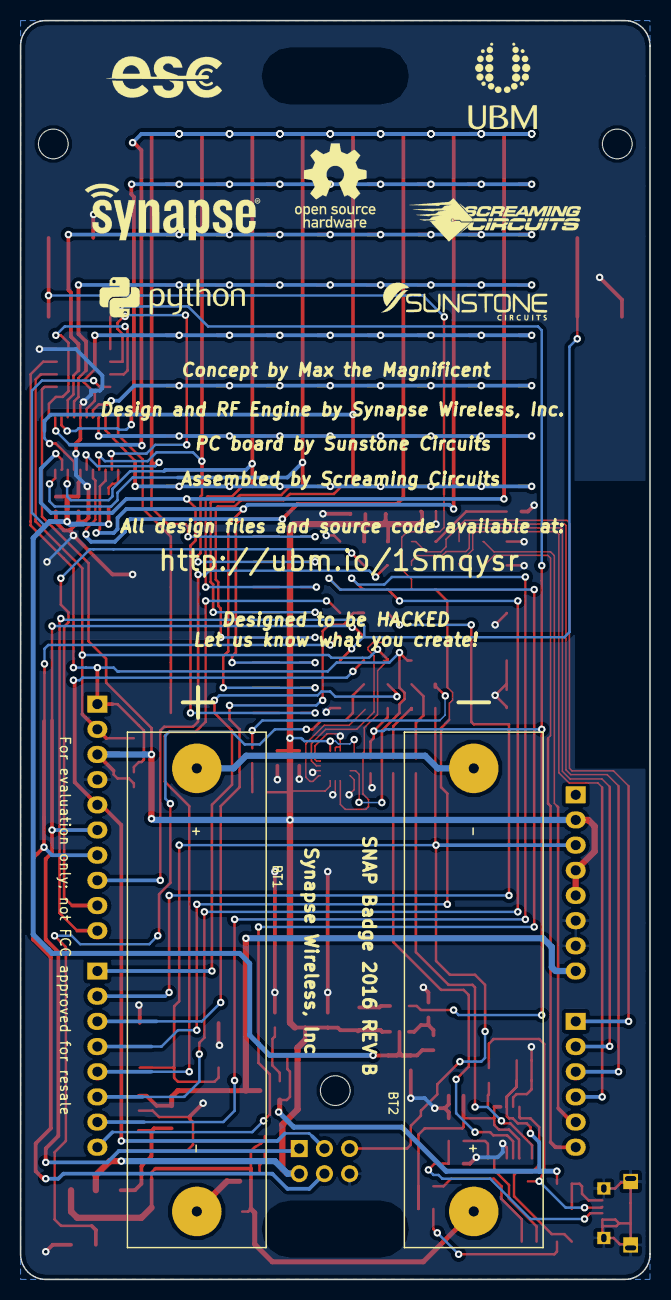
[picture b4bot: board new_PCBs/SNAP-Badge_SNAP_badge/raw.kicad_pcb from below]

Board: 2 copper layers, 63.5 x 127.0 mm, 141 parts (2 on the bottom side), 86 nets.

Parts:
BT1, BT2: 1.5V; BATT_2466
C1, C2, C10, C12, C14, C18, C20, C21: 0.1uF; C_0603
C3, C16: 10uF; C_0603
C4: 10nF; C_0603
C5, C6: 47pF; C_0603
C7, C8, C22, C23: 22uF; C_0603
C9, C11, C13, C15, C17, C19: 4.7uF; C_0603
D1, D3, D4, D5, D6, D7, D8, D9, D10, D11, D12, D13, D14, D15, D16, D17, D18, D19, D20, D21, D22, D23, D24, D25, D26, D27, D28, D29, D30, D31, D32, D33, D34, D35, D36, D37, D38, D39, D40, D41, D42, D43, D44, D45, D46, D47, D48, D49, D50, D51, D52, D53, D54, D55, D56, D57, D58, D59, D60, D61, D62, D63, D64, D65, D66, D67, D68: LED; Led_0603
D2, D69, D70, D71, D72, D73, D74, D75: 1N4148W; SOD-323
FB1: 600 OHM 500MA; R_0603
Fiducial_Mark: VAL**; Fiducial_Mark
Fiducial_Mark#2, Fiducial_Mark#3: VAL**; Fiducial_Mark
L1: 4.7uH 0.9A; TYS-2
P1: MicroB; USBmicroB
P2, P3: CONN_01X08; Socket_Strip_Straight_1x08
P4: CONN_01X10; Socket_Strip_Straight_1x10
P5: CONN_01X06; Socket_Strip_Straight_1x06
P6: CONN_02X03; Pin_Header_Straight_2x03
Q1: ZXMN2F30FHCT-ND; SOT-23
Q2: Si2305DS; SOT-23
R1: 10k; R_0603
R2, R3: 27; R_0603
R4, R5, R6: 270; R_0603
R7, R8: 1k; R_0603
R9: 200k; R_0603
R10, R12: 100k; R_0603
R11: 1M; R_0603
R13: 39k; R_0603
R14, R15, R16: 4.7k; R_0603
SW1: SWITCH_DPDT; SO-DPDT-6
SW2, SW3, SW4: SW_PUSH; SW_SPST_PTS645
SW5: SW_DIP_8; DIPSW-16
U1: SM220
U2: AS1115; QSOP-24
U3: FT230XS; SSOP-16_3.9x4.9mm_Pitch0.635mm
U4: LD1117S33CTR; SOT-223
U5: LIS3DH; LGA16_3x3
U6: TPS61070; TSOT-6-MK06A
U7: NLSX4373; SOIC-8_3.9x4.9mm_Pitch1.27mm

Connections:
/*IS_USB: SW1.5, U1.G2
/*RESET: P2.3, P6.5, SW4.2, U1.H5
/ACC_INT1: U1.E3, U5.11
/ACC_INT2: U1.H2, U5.9
/BTN_LFT: P4.10, SW3.2, U1.F1
/BTN_RT: SW2.2, U1.C4
/LED_matrix/DIG0: D3.1, D11.1, D19.1, D27.1, D35.1, D43.1, D51.1, D59.1, U2.2
/LED_matrix/DIG1: D4.1, D12.1, D20.1, D28.1, D36.1, D44.1, D52.1, D60.1, U2.3
/LED_matrix/DIG2: D5.1, D13.1, D21.1, D29.1, D37.1, D45.1, D53.1, D61.1, U2.4
/LED_matrix/DIG3: D6.1, D14.1, D22.1, D30.1, D38.1, D46.1, D54.1, D62.1, U2.5
/LED_matrix/DIG4: D7.1, D15.1, D23.1, D31.1, D39.1, D47.1, D55.1, D63.1, U2.7
/LED_matrix/DIG5: D8.1, D16.1, D24.1, D32.1, D40.1, D48.1, D56.1, D64.1, U2.8
/LED_matrix/DIG6: D9.1, D17.1, D25.1, D33.1, D41.1, D49.1, D57.1, D67.1, U2.9
/LED_matrix/DIG7: D10.1, D18.1, D26.1, D34.1, D42.1, D50.1, D58.1, D68.1, U2.10
/LED_matrix/LED_3V: C13.1, C14.1, C17.1, C19.1, R1.1, R11.1, U2.19, U6.5, U7.8
/LED_matrix/LED_SCL: U2.14, U7.6
/LED_matrix/LED_SDA: U2.1, U7.7
/LED_matrix/SEGA: D11.2, D12.2, D13.2, D14.2, D15.2, D16.2, D17.2, D18.2, D69.2, U2.15
/LED_matrix/SEGB: D19.2, D20.2, D21.2, D22.2, D23.2, D24.2, D25.2, D26.2, D70.2, U2.17
/LED_matrix/SEGC: D27.2, D28.2, D29.2, D30.2, D31.2, D32.2, D33.2, D34.2, D71.2, U2.20
/LED_matrix/SEGD: D35.2, D36.2, D37.2, D38.2, D39.2, D40.2, D41.2, D42.2, D72.2, U2.23
/LED_matrix/SEGDP: D2.2, D3.2, D4.2, D5.2, D6.2, D7.2, D8.2, D9.2, D10.2, U2.22
/LED_matrix/SEGE: D43.2, D44.2, D45.2, D46.2, D47.2, D48.2, D49.2, D50.2, D73.2, U2.21
/LED_matrix/SEGF: D51.2, D52.2, D53.2, D54.2, D55.2, D56.2, D57.2, D58.2, D74.2, U2.16
/LED_matrix/SEGG: D59.2, D60.2, D61.2, D62.2, D63.2, D64.2, D67.2, D68.2, D75.2, U2.18
/MISO: P4.6, P6.1, U1.E2
/MOSI: P4.7, P6.4, U1.E1
/PB5: P3.5, U1.D1
/PB6: P3.3, U1.D2
/PB7: P3.2, U1.D3
/PD4: P3.1, U1.G3
/PE0: P3.8, U1.C1
/PE1: P3.7, U1.C2
/PE3: P4.9, U1.B2
/PE4: P3.6, U1.C3
/PE5: P4.8, U1.B3
/PE7: P3.4, U1.C5
/PF0: P5.1, U1.A4
/PF1: P5.2, U1.B4
/PF4: P5.3, U1.A6
/PF5: P5.4, U1.B6
/PF6: P5.5, U1.A7
/PF7: P5.6, U1.B7
/RXLED: D66.1, U3.7
/SCLK: P4.5, P6.3, U1.F2
/STATUS_LED: D1.1, U1.G5
/TXLED: D65.1, U3.14
/USB_RXD: R8.2, U1.H4
/USB_TXD: R7.2, U1.G4
/VIN_USB: C11.1, C12.1, C21.1, FB1.2, Q2.2, U3.12
/VREG_IN: C2.1, P2.8, Q2.3, U4.3
GND: C1.2, C2.2, C3.2, C4.2, C5.2, C6.2, C7.2, C8.2, C9.2, C10.2, C11.2, C12.2, C13.2, C14.2, C15.2, C16.2, C17.2, C18.2, C19.2, C20.2, C22.2, C23.2, P1.4, P1.5, P1.6, P2.6, P2.7, P4.4, P6.6, Q1.2, R9.1, R10.1, R13.1, R16.2, SW1.6, SW2.1, SW3.1, SW4.1, U1.A1, U1.A8, U1.B8, U1.D8, U1.F8, U1.G1, U1.G8, U1.H1, U1.H8, U2.6, U3.5, U3.13, U4.1, U5.5, U5.7, U5.10, U5.12, U5.13, U5.15, U5.16, U6.2, U7.4
I2C_SCL: P4.1, R15.2, U1.F4, U5.4, U7.3
I2C_SDA: P4.2, R14.2, U1.F3, U5.6, U7.2
LED_PWR_EN: R10.2, U1.H3, U6.3, U7.5
unnamed: BT1.1, BT2.2
unnamed: BT1.2, Q1.3
unnamed: BT2.1, C8.1, C20.1, R12.1, SW1.1
unnamed: C1.1, C15.1, R4.1, R5.1, U3.3, U3.10, U3.11
unnamed: C3.1, SW1.3, U4.2
unnamed: C4.1, FB1.1, P1.1
unnamed: C5.1, P1.2, R3.2
unnamed: C6.1, P1.3, R2.2
unnamed: C21.2, Q2.1, R13.2
unnamed: D1.2, R6.2
unnamed: D2.1, SW5.8
unnamed: D65.2, R4.2
unnamed: D66.2, R5.2
unnamed: D69.1, SW5.7
unnamed: D70.1, SW5.6
unnamed: D71.1, SW5.5
unnamed: D72.1, SW5.4
unnamed: D73.1, SW5.3
unnamed: D74.1, SW5.2
unnamed: D75.1, SW5.1
unnamed: L1.1, U6.1
unnamed: Q1.1, R12.2
unnamed: R1.2, U2.13
unnamed: R2.1, U3.8
unnamed: R3.1, U3.9
unnamed: R7.1, U3.1
unnamed: R8.1, U3.4
unnamed: R9.2, R11.2, U6.4
unnamed: R16.1, U1.A5
unnamed: SW5.9, SW5.10, SW5.11, SW5.12, SW5.13, SW5.14, SW5.15, SW5.16, U2.12
VCC: C7.1, C9.1, C10.1, C16.1, C18.1, C22.1, C23.1, L1.2, P2.2, P2.4, P2.5, P4.3, P6.2, R6.1, R14.1, R15.1, SW1.2, U1.A2, U1.A3, U5.1, U5.8, U5.14, U6.6, U7.1
